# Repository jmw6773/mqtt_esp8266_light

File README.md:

# MQTT RBG Controller for the ESP8266

This project was based on the esp-mqtt-rgb-led project by Corban Mailloux:<br>
 https://github.com/corbanmailloux/esp-mqtt-rgb-led

v0.1.0 - Removed IOTAppStory and added HTML web status and config page<br>
v0.1.1 - Memory leak fix (?), random bug fixes, added random color on turn on if no color/transistion defined<br>
 *** Don't update to ESP Board 2.4.2  until confirm OTA is fixed<br>
 ***   https://github.com/esp8266/Arduino/issues/5023<br>

### *** ESP Core File Changes ***

File:<br>
  ~\AppData\Local\Arduino15\packages\esp8266\hardware\esp8266\2.4.2\libraries\ESP8266WebServer\src\detail\RequestHandlersImpl.h

 Change the following in function 'bool handle(...)'<br>
  -- this fixes serving gz files when they exist instead of the uncompressed file<br>

## ESP Version 4.2
```C
if (!path.endsWith(FPSTR(mimeTable[gz].endsWith)) && !_fs.exists(path))
{
  String pathWithGz = path + FPSTR(mimeTable[gz].endsWith);
  if(_fs.exists(pathWithGz))
  path += FPSTR(mimeTable[gz].endsWith);
}

if (!path.endsWith(FPSTR(mimeTable[gz].endsWith)) { //&& !_fs.exists(path))
{
  String pathWithGz = path + FPSTR(mimeTable[gz].endsWith);
  if(_fs.exists(pathWithGz))
  path += FPSTR(mimeTable[gz].endsWith);
}
```

## ESP Version 4.0
```C
if (!path.endsWith(".gz") && !_fs.exists(path))
{
  String pathWithGz = path + ".gz";
  if(_fs.exists(pathWithGz))
    path += ".gz";
}

if (!path.endsWith(".gz"))// && !_fs.exists(path))
{
  String pathWithGz = path + ".gz";
  if(_fs.exists(pathWithGz))
    path += ".gz";
}# mqtt_esp8266_light
```

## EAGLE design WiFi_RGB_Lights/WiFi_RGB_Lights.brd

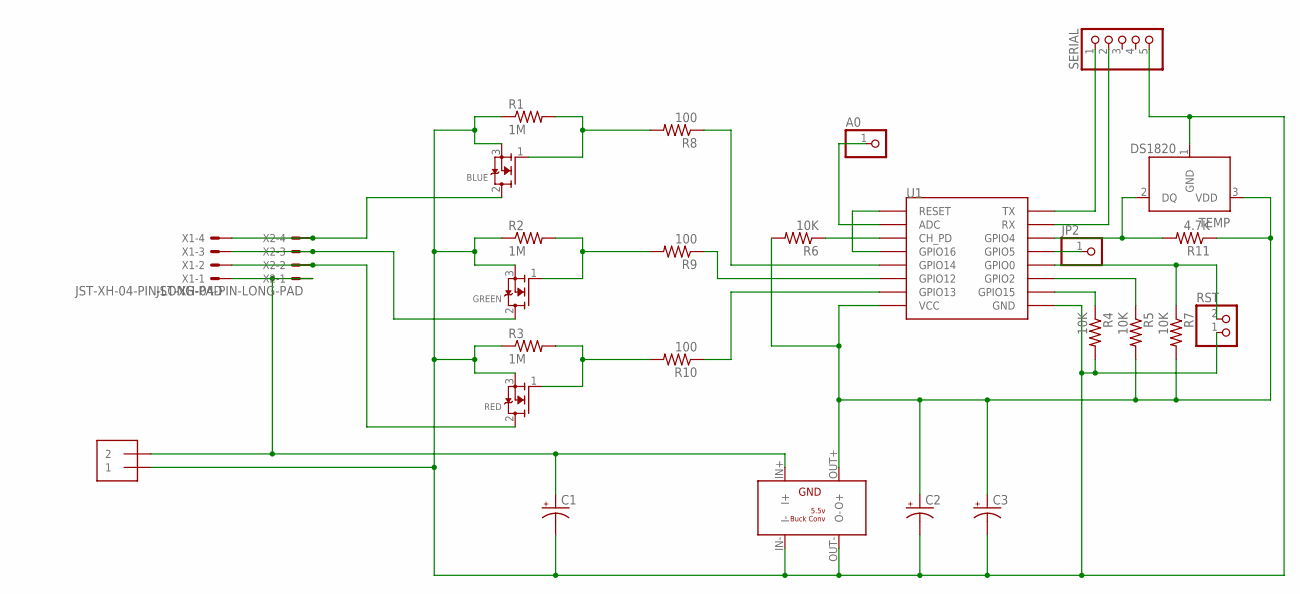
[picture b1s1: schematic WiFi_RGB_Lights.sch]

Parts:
3.3V: BUCK_CONV_5.5V; BUCK_CONV
A0: PINHD-1X1; 1X01
BLUE: MOSFET-NGDS_TO220V; TO220V
C1: CPOL-USE5-8.5; E5-8,5
C2, C3: CPOL-USE2.5-6; E2,5-6
GREEN: MOSFET-NGDS_TO220V; TO220V
JP2: PINHD-1X1; 1X01
PWR: 5MM_TERMINAL_BLOCK
R1, R2, R3: 1M; 1206
R4, R5, R6, R7: 10K; 1206
R8, R9, R10: 100; 0805
R11: 4.7K; 1206
RED: MOSFET-NGDS_TO220V; TO220V
RST: JST_2PIN-THM; JST-PH-2-THM
SERIAL: PINHD-1X5; 1X05
TEMP: DS1820; TO-92
U1: ESP12
X1, X2: JST-XH-04-PIN-LONG-PAD; JST-XH-04-PACKAGE-LONG-PAD

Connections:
3V: 3.3V.OUT+ (O+), C2.+, C3.+, R5.2, R6.2, R7.2, R11.1, TEMP.3 (VDD), U1.VCC
12V: 3.3V.IN+ (I+), C1.+, PWR.2, X1.1, X2.1
GND: 3.3V.IN- (I-), 3.3V.OUT- (O-), BLUE.3 (S), C1.-, C2.-, C3.-, GREEN.3 (S), PWR.1, R1.1, R2.1, R3.1, R4.2, RED.3 (S), RST.1 (2), SERIAL.5, TEMP.1 (GND), U1.GND
unnamed: GREEN.1 (G), R2.2, R9.2
unnamed: U1.GPIO16, U1.RESET
unnamed: R6.1, U1.CH_PD
unnamed: R10.1, U1.GPIO13
unnamed: R9.1, U1.GPIO12
unnamed: R8.1, U1.GPIO14
unnamed: A0.1, U1.ADC
unnamed: R4.1, U1.GPIO15
unnamed: BLUE.1 (G), R1.2, R8.2
unnamed: R5.1, U1.GPIO2
unnamed: R7.1, RST.2 (1), U1.GPIO0
unnamed: RED.2 (D), X1.2, X2.2
unnamed: R11.2, TEMP.2 (DQ), U1.GPIO4
unnamed: JP2.1, U1.GPIO5
unnamed: SERIAL.2, U1.RX
unnamed: SERIAL.1, U1.TX
unnamed: R3.2, R10.2, RED.1 (G)
unnamed: GREEN.2 (D), X1.3, X2.3
unnamed: BLUE.2 (D), X1.4, X2.4

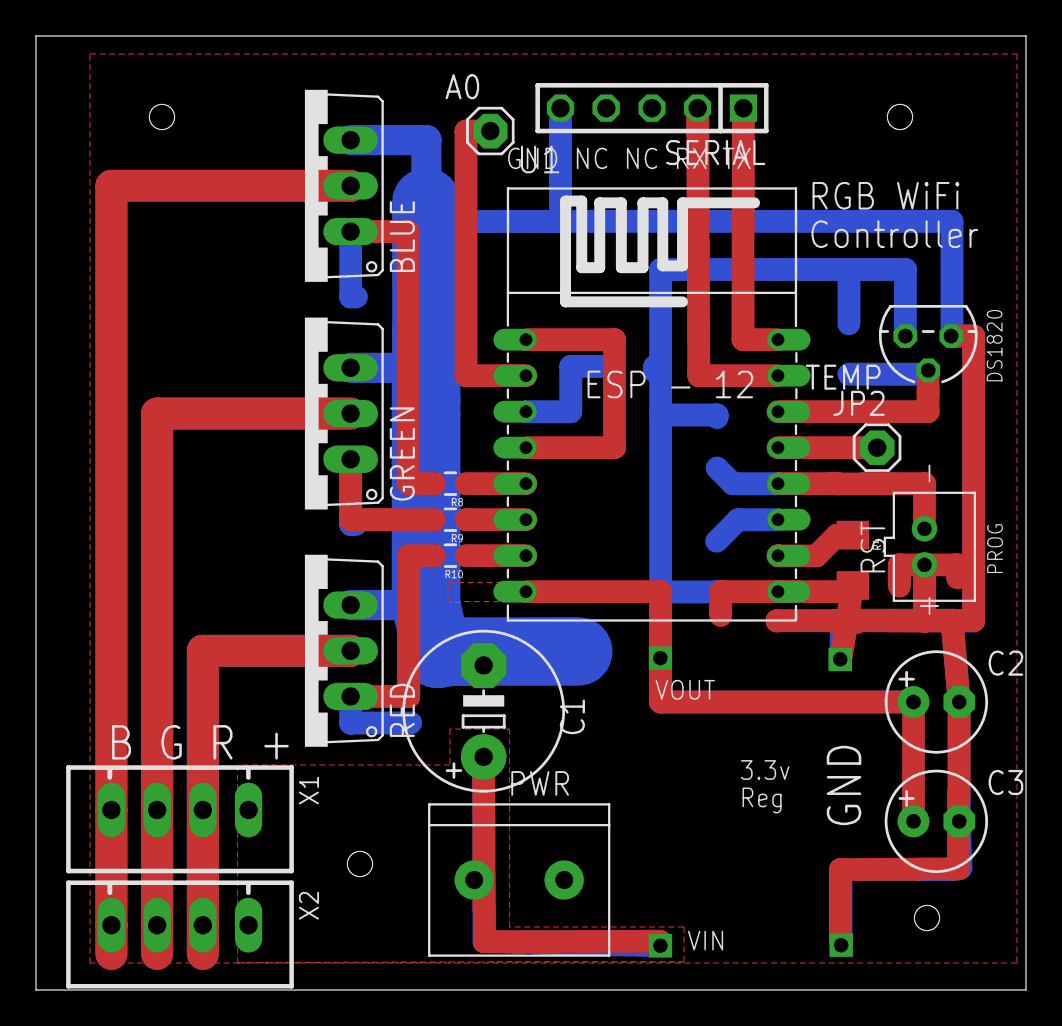
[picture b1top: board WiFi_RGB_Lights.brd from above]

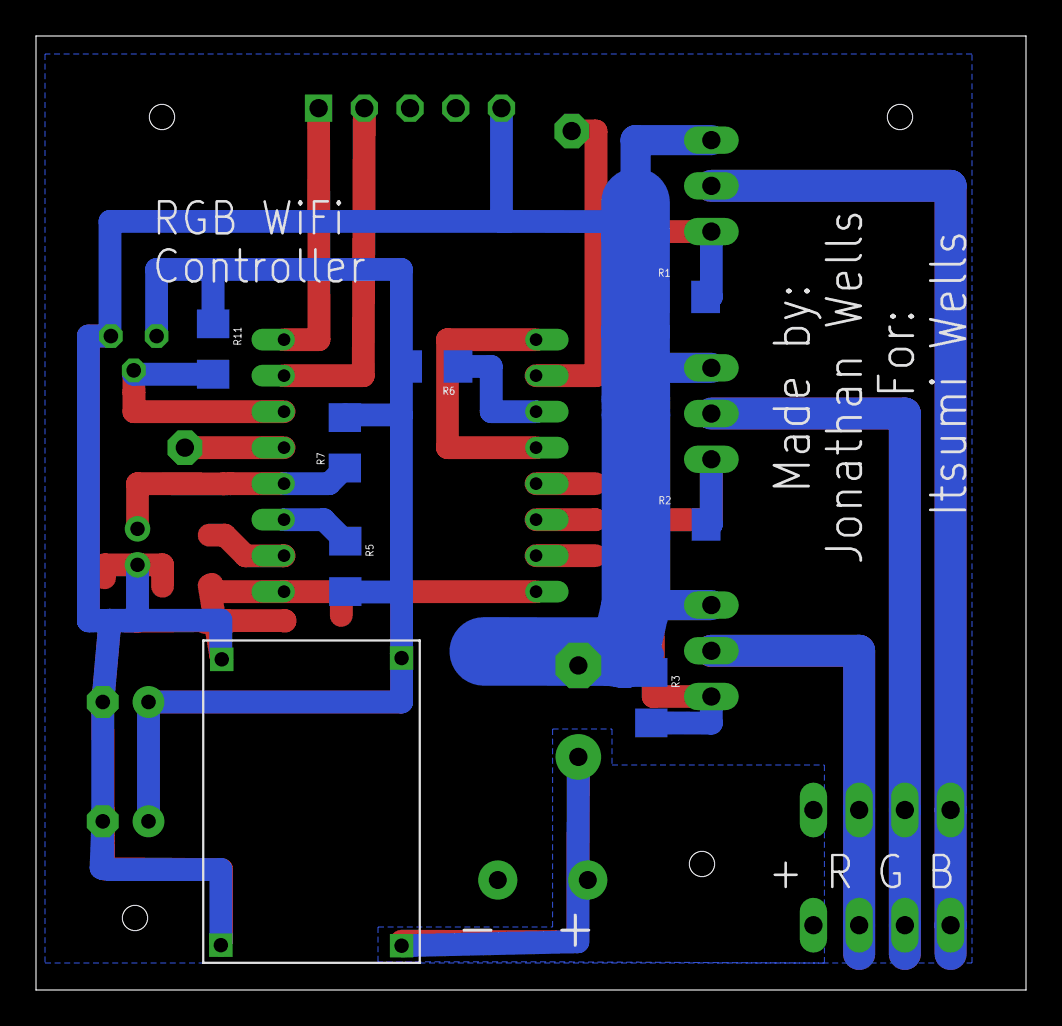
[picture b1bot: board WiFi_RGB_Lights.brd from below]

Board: 2 copper layers, 55.0 x 53.0 mm, 27 parts (8 on the bottom side), 22 nets.

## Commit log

2018-10-02 remove compiled binary
2018-10-02 Add PCB and pictures
2018-11-22 Revampt many things

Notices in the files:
parts and their libraries:
SparkFun-Passives: Licensing: Creative Commons ShareAlike 4.0 International - https://creativecommons.org/licenses/by-sa/4.0
